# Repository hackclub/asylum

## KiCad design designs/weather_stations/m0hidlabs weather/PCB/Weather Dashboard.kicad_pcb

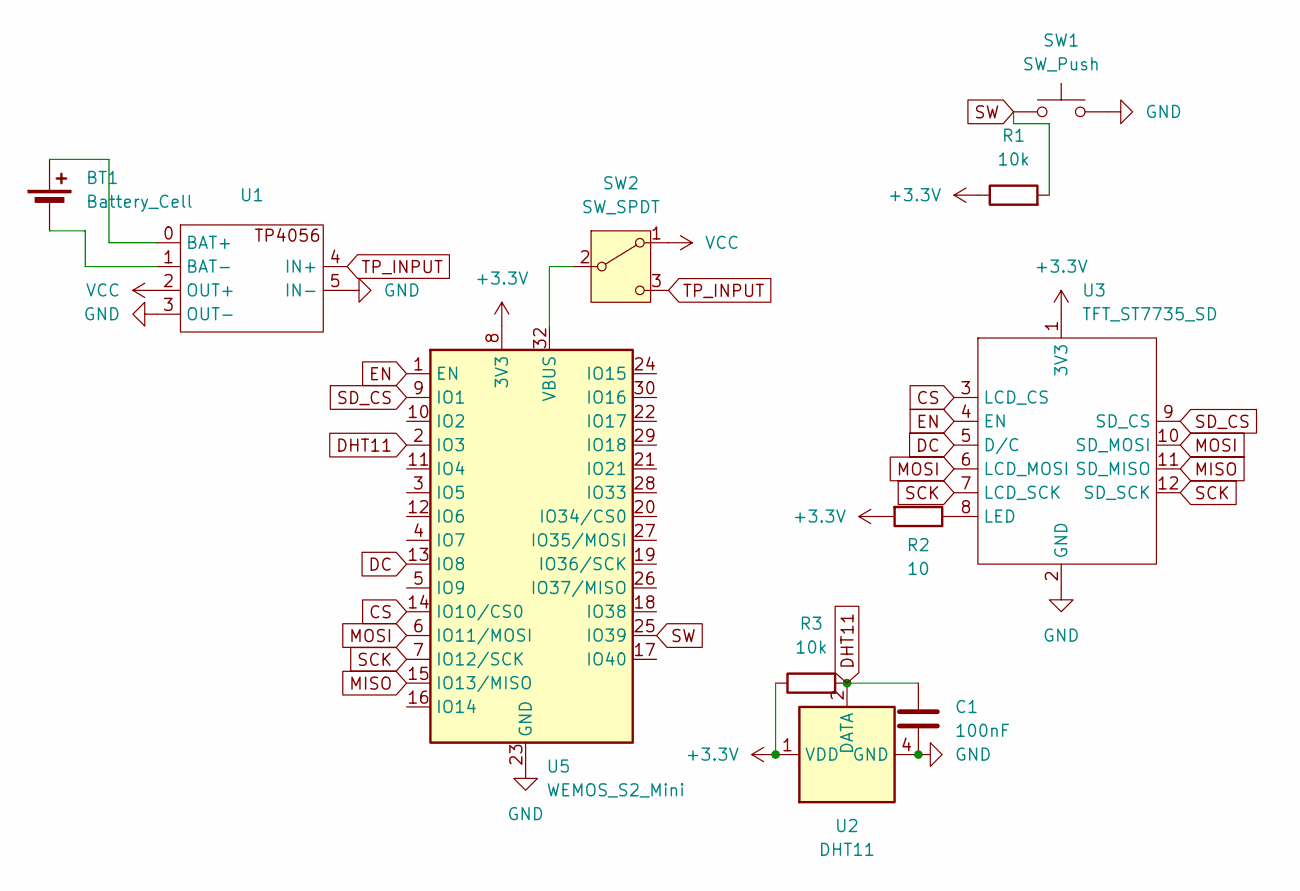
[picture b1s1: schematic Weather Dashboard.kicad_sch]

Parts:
BT1: Battery_Cell; PinHeader_1x02_P2.54mm_Vertical_swapped
C1: 100nF; C_0805_2012Metric_Pad1.18x1.45mm_HandSolder
R1, R3: 10k; R_Axial_DIN0207_L6.3mm_D2.5mm_P10.16mm_Horizontal
R2: 10; R_0805_2012Metric_Pad1.20x1.40mm_HandSolder
SW1: SW_Push; SW_PUSH_6mm
SW2: SW_SPDT; SW_Slide-03_Wuerth-WS-SLTV_10x2.5x6.4_P2.54mm
U1: TP4056
U2: DHT11; Aosong_DHT11_5.5x12.0_P2.54mm
U3: TFT_ST7735_SD
U5: WEMOS_S2_Mini

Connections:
+3.3V: R1.1, R2.2, R3.1, U2.1 (VDD), U3.1 (3V3), U5.8 (3V3)
CS: U3.3 (LCD_CS), U5.14 (IO10/CS0)
DC: U3.5 (D/C), U5.13 (IO8)
DHT11: C1.1, R3.2, U2.2 (DATA), U5.2 (IO3)
EN: U3.4 (EN), U5.1 (EN)
GND: C1.2, SW1.2, U1.3 (OUT-), U1.5 (IN-), U2.4 (GND), U3.2 (GND), U5.23 (GND)
MISO: U3.11 (SD_MISO), U5.15 (IO13/MISO)
MOSI: U3.6 (LCD_MOSI), U3.10 (SD_MOSI), U5.6 (IO11/MOSI)
unnamed: BT1.1 (+), U1.0 (BAT+)
unnamed: BT1.2 (-), U1.1 (BAT-)
unnamed: SW2.2 (B), U5.32 (VBUS)
unnamed: R2.1, U3.8 (LED)
SCK: U3.7 (LCD_SCK), U3.12 (SD_SCK), U5.7 (IO12/SCK)
SD_CS: U3.9 (SD_CS), U5.9 (IO1)
SW: R1.2, SW1.1, U5.25 (IO39)
TP_INPUT: SW2.3 (C), U1.4 (IN+)
VCC: SW2.1 (A), U1.2 (OUT+)

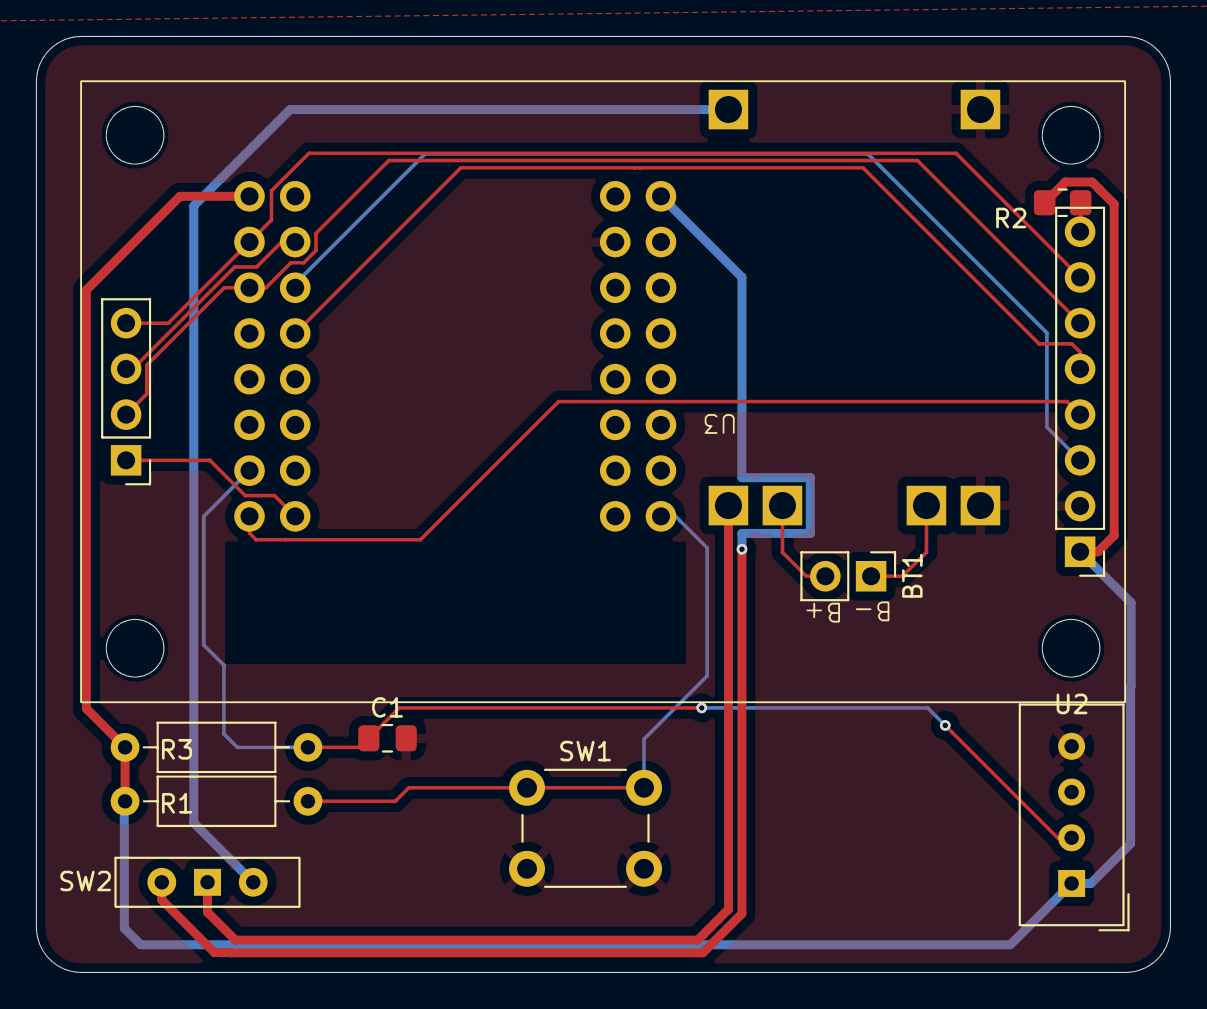
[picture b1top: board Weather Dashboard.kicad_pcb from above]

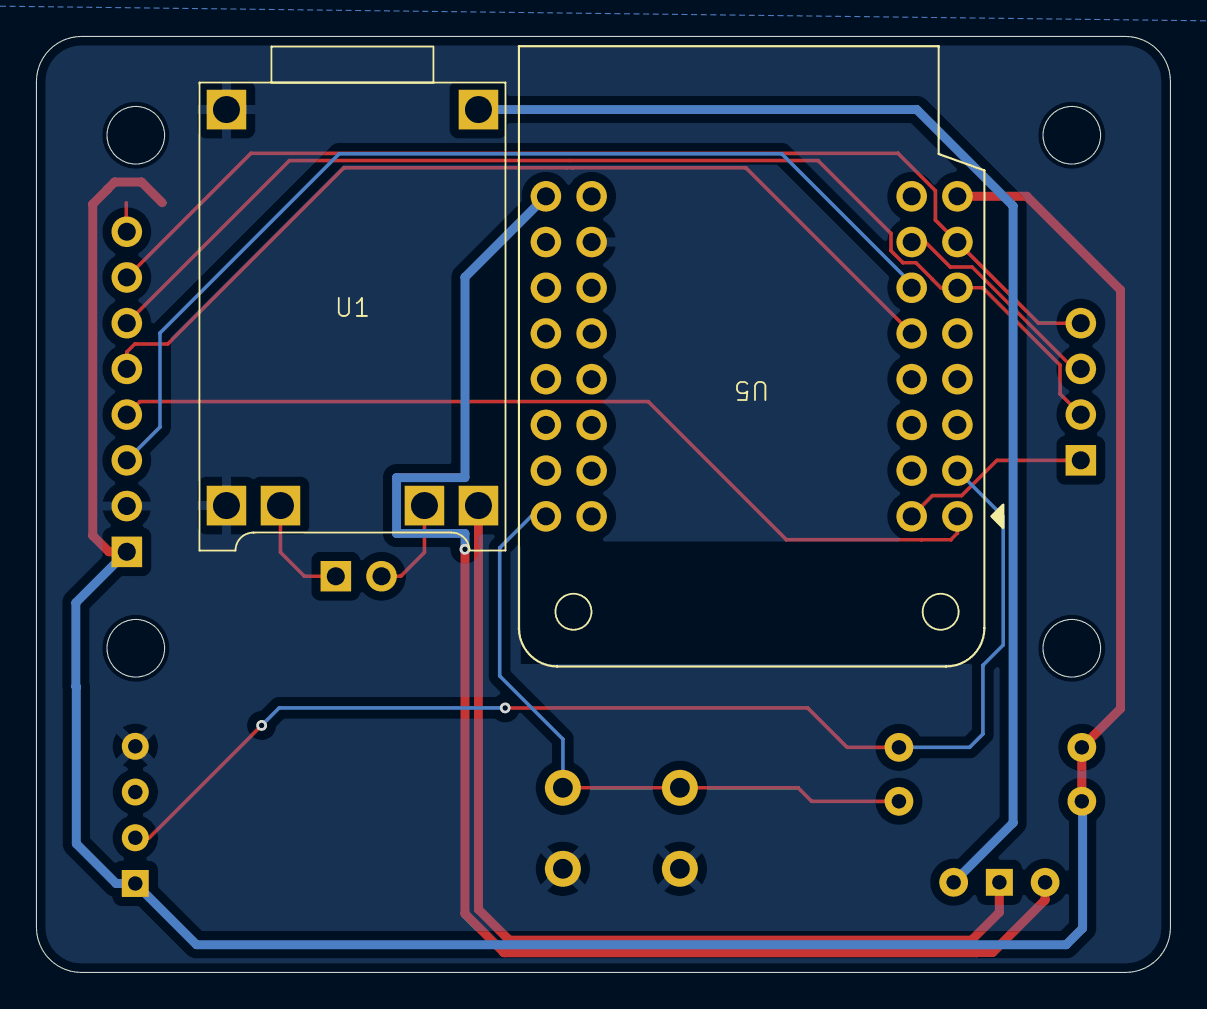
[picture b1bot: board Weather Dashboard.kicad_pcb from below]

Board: 2 copper layers, 63.0 x 52.0 mm, 11 parts (2 on the bottom side), 17 nets.

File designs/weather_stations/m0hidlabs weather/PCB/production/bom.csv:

Designator,Footprint,Quantity,Value,LCSC Part #
BT1,PinHeader_1x02_P2.54mm_Vertical_swapped,1,Battery_Cell,
C1,0805,1,100nF,
"R1, R3",R_Axial_DIN0207_L6.3mm_D2.5mm_P10.16mm_Horizontal,2,10k,
R2,0805,1,10,
SW1,SW_PUSH_6mm,1,SW_Push,
SW2,SW_Slide-03_Wuerth-WS-SLTV_10x2.5x6.4_P2.54mm,1,SW_SPDT,
U1,TP4056,1,~,
U2,Aosong_DHT11_5.5x12.0_P2.54mm,1,DHT11,
U3,TFT_ST7735_SD,1,TFT_ST7735_SD,
U5,WEMOS_S2_Mini,1,WEMOS_S2_Mini,

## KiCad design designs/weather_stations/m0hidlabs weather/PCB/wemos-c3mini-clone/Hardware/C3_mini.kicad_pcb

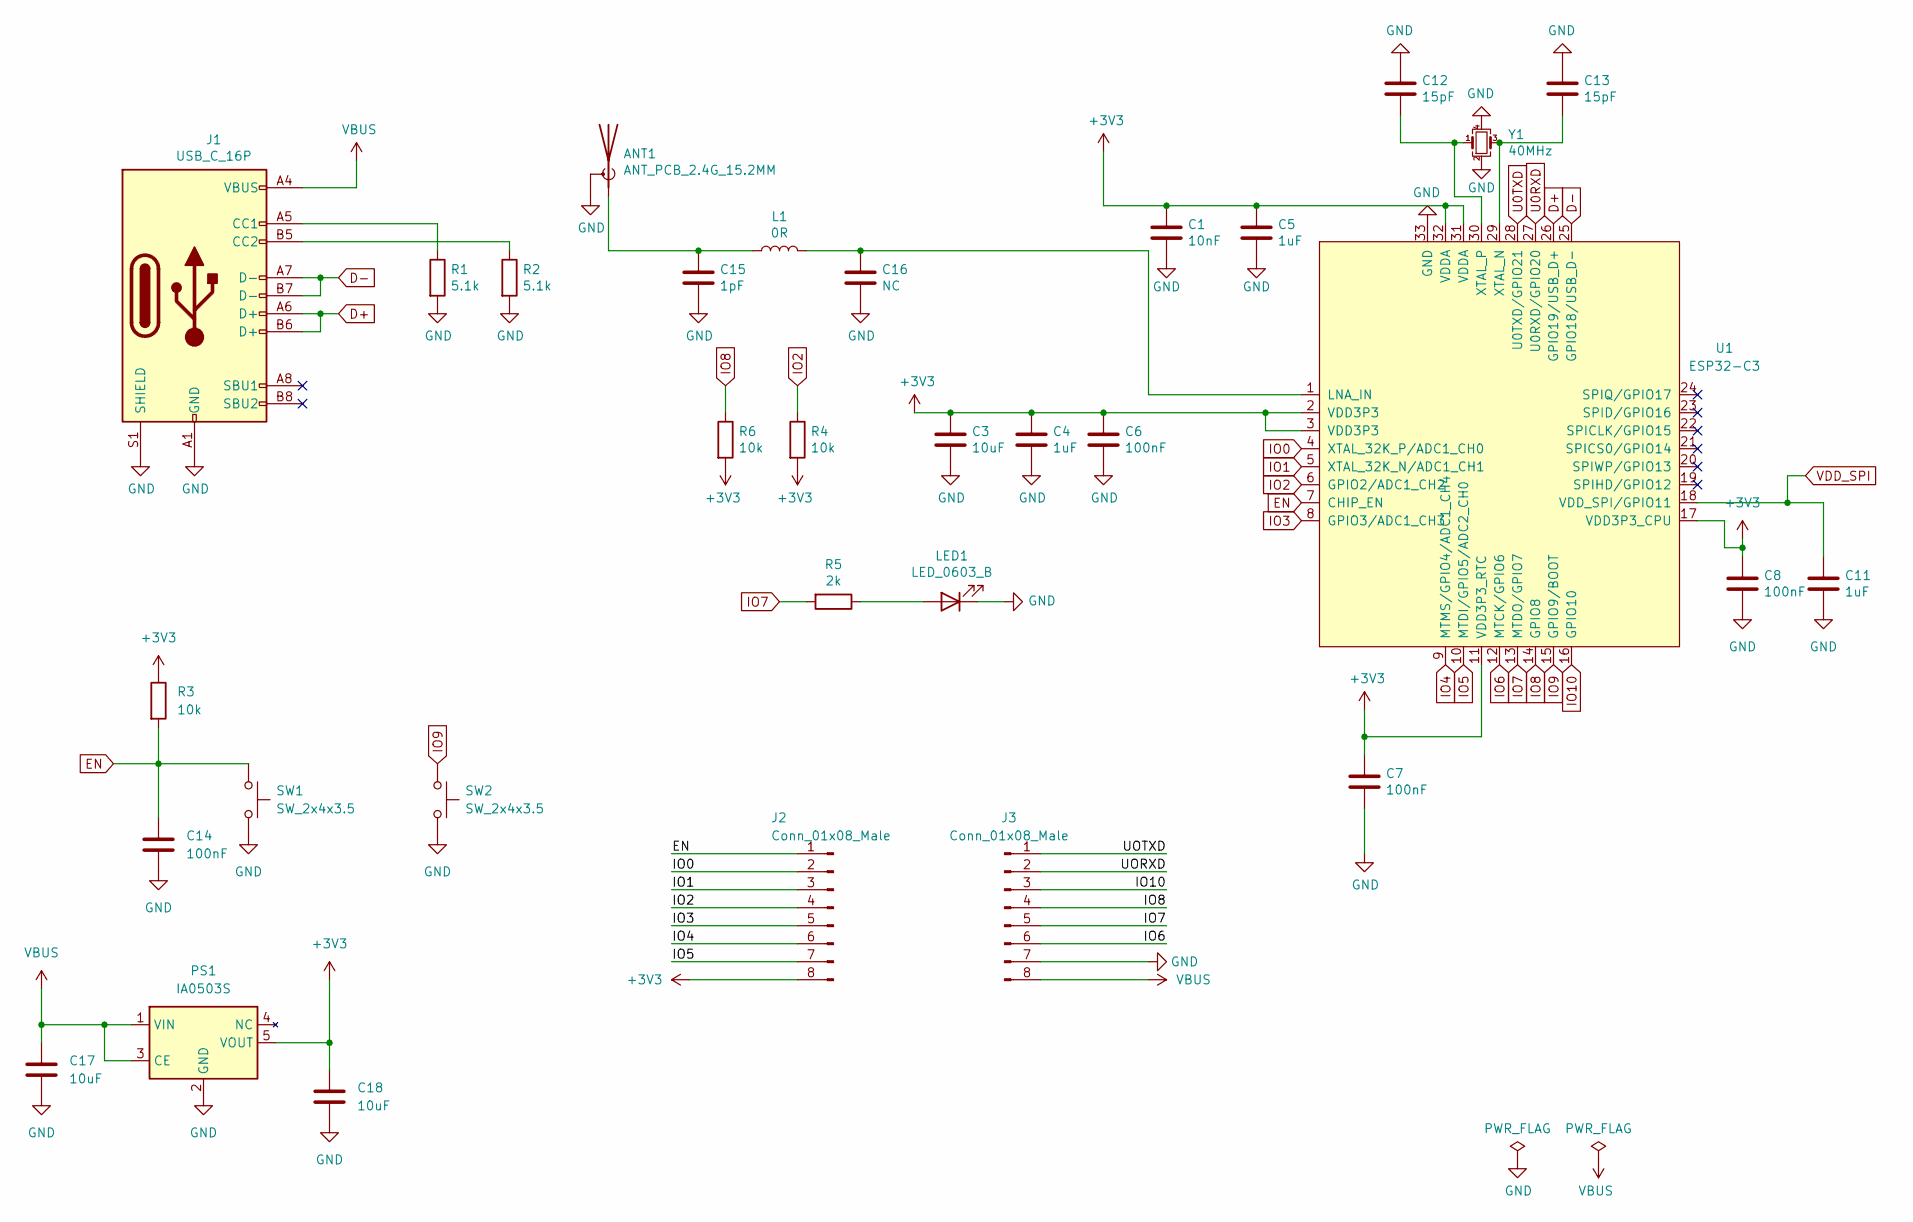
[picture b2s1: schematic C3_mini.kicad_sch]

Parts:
ANT1: ANT_PCB_2.4G_15.2MM; Texas_SWRA117D_2.4GHz_Right
C1: 10nF; C_0402_1005Metric
C3, C17, C18: 10uF; C_0603_1608Metric
C4, C5, C11: 1uF; C_0402_1005Metric
C6, C7, C8, C14: 100nF; C_0402_1005Metric
C12, C13: 15pF; C_0402_1005Metric
C15: 1pF; C_0402_1005Metric
C16: NC; C_0402_1005Metric
J1: USB_C_16P; USB_C_Receptacle_Palconn_UTC16-G
J2, J3: Conn_01x08_Male
L1: 0R; L_0603_1608Metric
LED1: LED_0603_B; LED_0603_1608Metric
PS1: IA0503S; SOT-23-5
R1, R2: 5.1k; R_0402_1005Metric
R3, R4, R6: 10k; R_0402_1005Metric
R5: 2k; R_0402_1005Metric
SW1, SW2: SW_2x4x3.5; ST-1114A
U1: ESP32-C3; QFN-32-1EP_5x5mm_P0.5mm_EP3.45x3.45mm
Y1: 40MHz; Crystal_SMD_TXC_7M-4Pin_3.2x2.5mm

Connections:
+3V3: C1.1, C3.1, C4.1, C5.1, C6.1, C7.1, C8.1, C18.1, J2.8, PS1.5 (VOUT), R3.1, R4.2, R6.2, U1.2 (VDD3P3), U1.3 (VDD3P3), U1.11 (VDD3P3_RTC), U1.17 (VDD3P3_CPU), U1.31 (VDDA), U1.32 (VDDA)
D+: J1.A6 (D+), J1.B6 (D+), U1.26 (GPIO19/USB_D+)
D-: J1.A7 (D-), J1.B7 (D-), U1.25 (GPIO18/USB_D-)
EN: C14.1, J2.1, R3.2, SW1.1, U1.7 (CHIP_EN)
GND: ANT1.2 (Shield), C1.2, C3.2, C4.2, C5.2, C6.2, C7.2, C8.2, C11.2, C12.1, C13.1, C14.2, C15.2, C16.2, C17.2, C18.2, J1.A1 (GND), J1.A12 (GND), J1.B1 (GND), J1.B12 (GND), J1.S1 (SHIELD), J3.7, LED1.1 (K), PS1.2 (GND), R1.2, R2.2, SW1.2, SW2.2, U1.33 (GND), Y1.2, Y1.4
IO0: J2.2, U1.4 (XTAL_32K_P/ADC1_CH0)
IO1: J2.3, U1.5 (XTAL_32K_N/ADC1_CH1)
IO2: J2.4, R4.1, U1.6 (GPIO2/ADC1_CH2)
IO3: J2.5, U1.8 (GPIO3/ADC1_CH3)
IO4: J2.6, U1.9 (MTMS/GPIO4/ADC1_CH4)
IO5: J2.7, U1.10 (MTDI/GPIO5/ADC2_CH0)
IO6: J3.6, U1.12 (MTCK/GPIO6)
IO7: J3.5, R5.2, U1.13 (MTDO/GPIO7)
IO8: J3.4, R6.1, U1.14 (GPIO8)
IO9: SW2.1, U1.15 (GPIO9/BOOT)
IO10: J3.3, U1.16 (GPIO10)
unnamed: ANT1.1 (A), C15.1, L1.1
unnamed: C12.2, U1.30 (XTAL_P), Y1.1
unnamed: C13.2, U1.29 (XTAL_N), Y1.3
unnamed: C16.1, L1.2, U1.1 (LNA_IN)
unnamed: J1.A5 (CC1), R1.1
unnamed: J1.B5 (CC2), R2.1
unnamed: LED1.2 (A), R5.1
VBUS: C17.1, J1.A4 (VBUS), J1.A9 (VBUS), J1.B4 (VBUS), J1.B9 (VBUS), J3.8, PS1.1 (VIN), PS1.3 (CE)
VDD_SPI: C11.1, U1.18 (VDD_SPI/GPIO11)

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
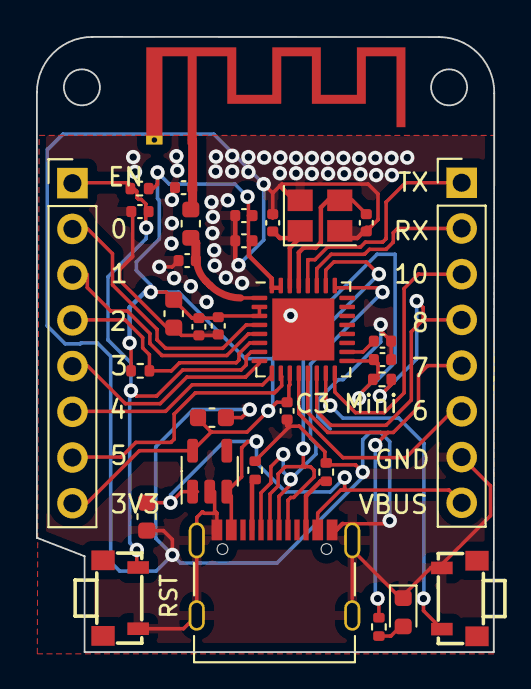
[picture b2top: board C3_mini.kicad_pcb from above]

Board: 2 copper layers, 25.4 x 34.2 mm, 32 parts (0 on the bottom side), 27 nets.

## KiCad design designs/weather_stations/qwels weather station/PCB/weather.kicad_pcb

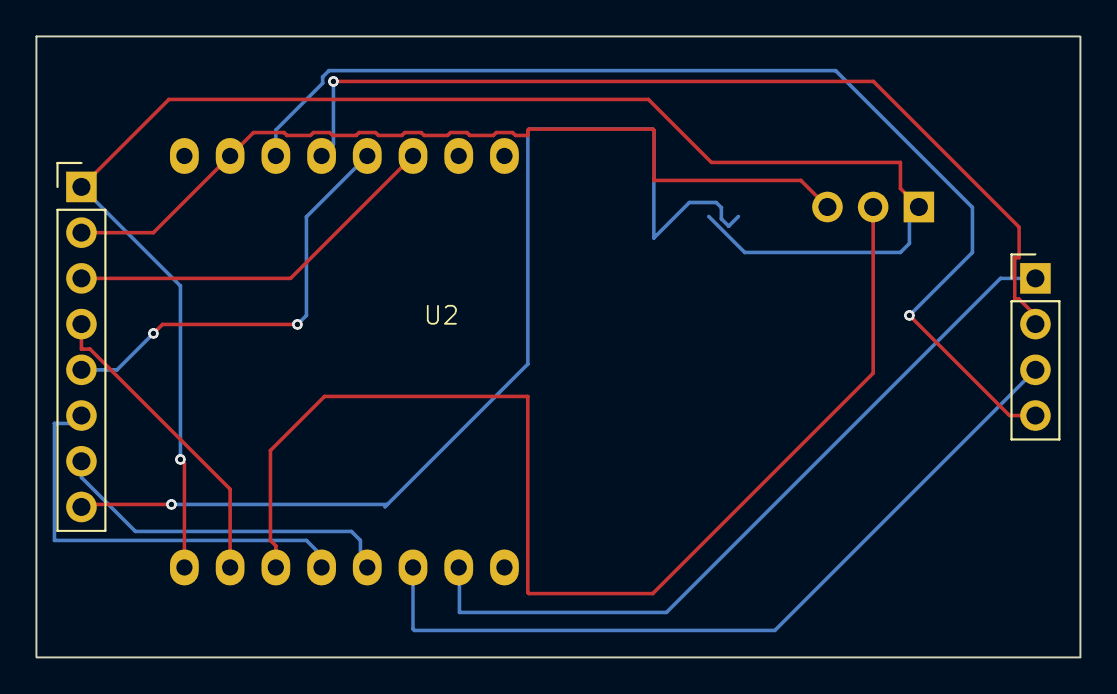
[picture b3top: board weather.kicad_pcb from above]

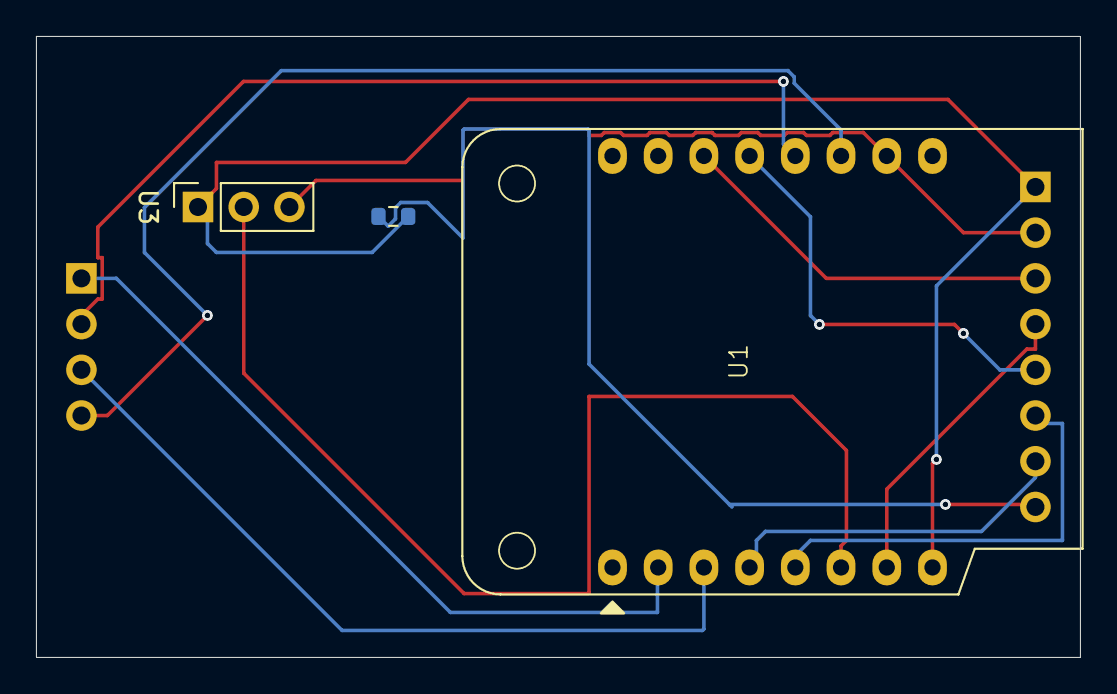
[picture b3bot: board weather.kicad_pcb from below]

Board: 2 copper layers, 58.0 x 34.5 mm, 4 parts (3 on the bottom side), 13 nets.

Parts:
R1: R; R_0603_1608Metric
U1: WEMOS_C3_Mini; WEMOS_C3_mini
U2: TFT_ST7735_SD
U3: AM2302; DHT11

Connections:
3v: R1.1, U1.8 (3V3), U2.1 (3V3), U3.1 (VDD)
MISO: U1.3 (MISO/IO2), U2.11 (SD_MISO)
MOSI: U1.12 (MOSI/IO7), U2.10 (SD_MOSI)
unnamed: U1.14 (CS0/IO10), U2.3 (LCD_CS)
unnamed: U1.5 (IO0), U2.6 (LCD_MOSI)
unnamed: U1.4 (IO1), U2.7 (LCD_SCK)
unnamed: U1.7 (IO5), U2.4 (EN)
unnamed: U1.13 (IO8), U2.5 (D/C)
unnamed: R1.2, U2.8 (LED)
SCK: U1.11 (SCK/IO6), U2.12 (SD_SCK)
SDA: U1.6 (IO4), U3.2 (SDA)
cs: U1.2 (IO3), U2.9 (SD_CS)
gnd: U1.10 (GND), U2.2 (GND), U3.3 (GND)
